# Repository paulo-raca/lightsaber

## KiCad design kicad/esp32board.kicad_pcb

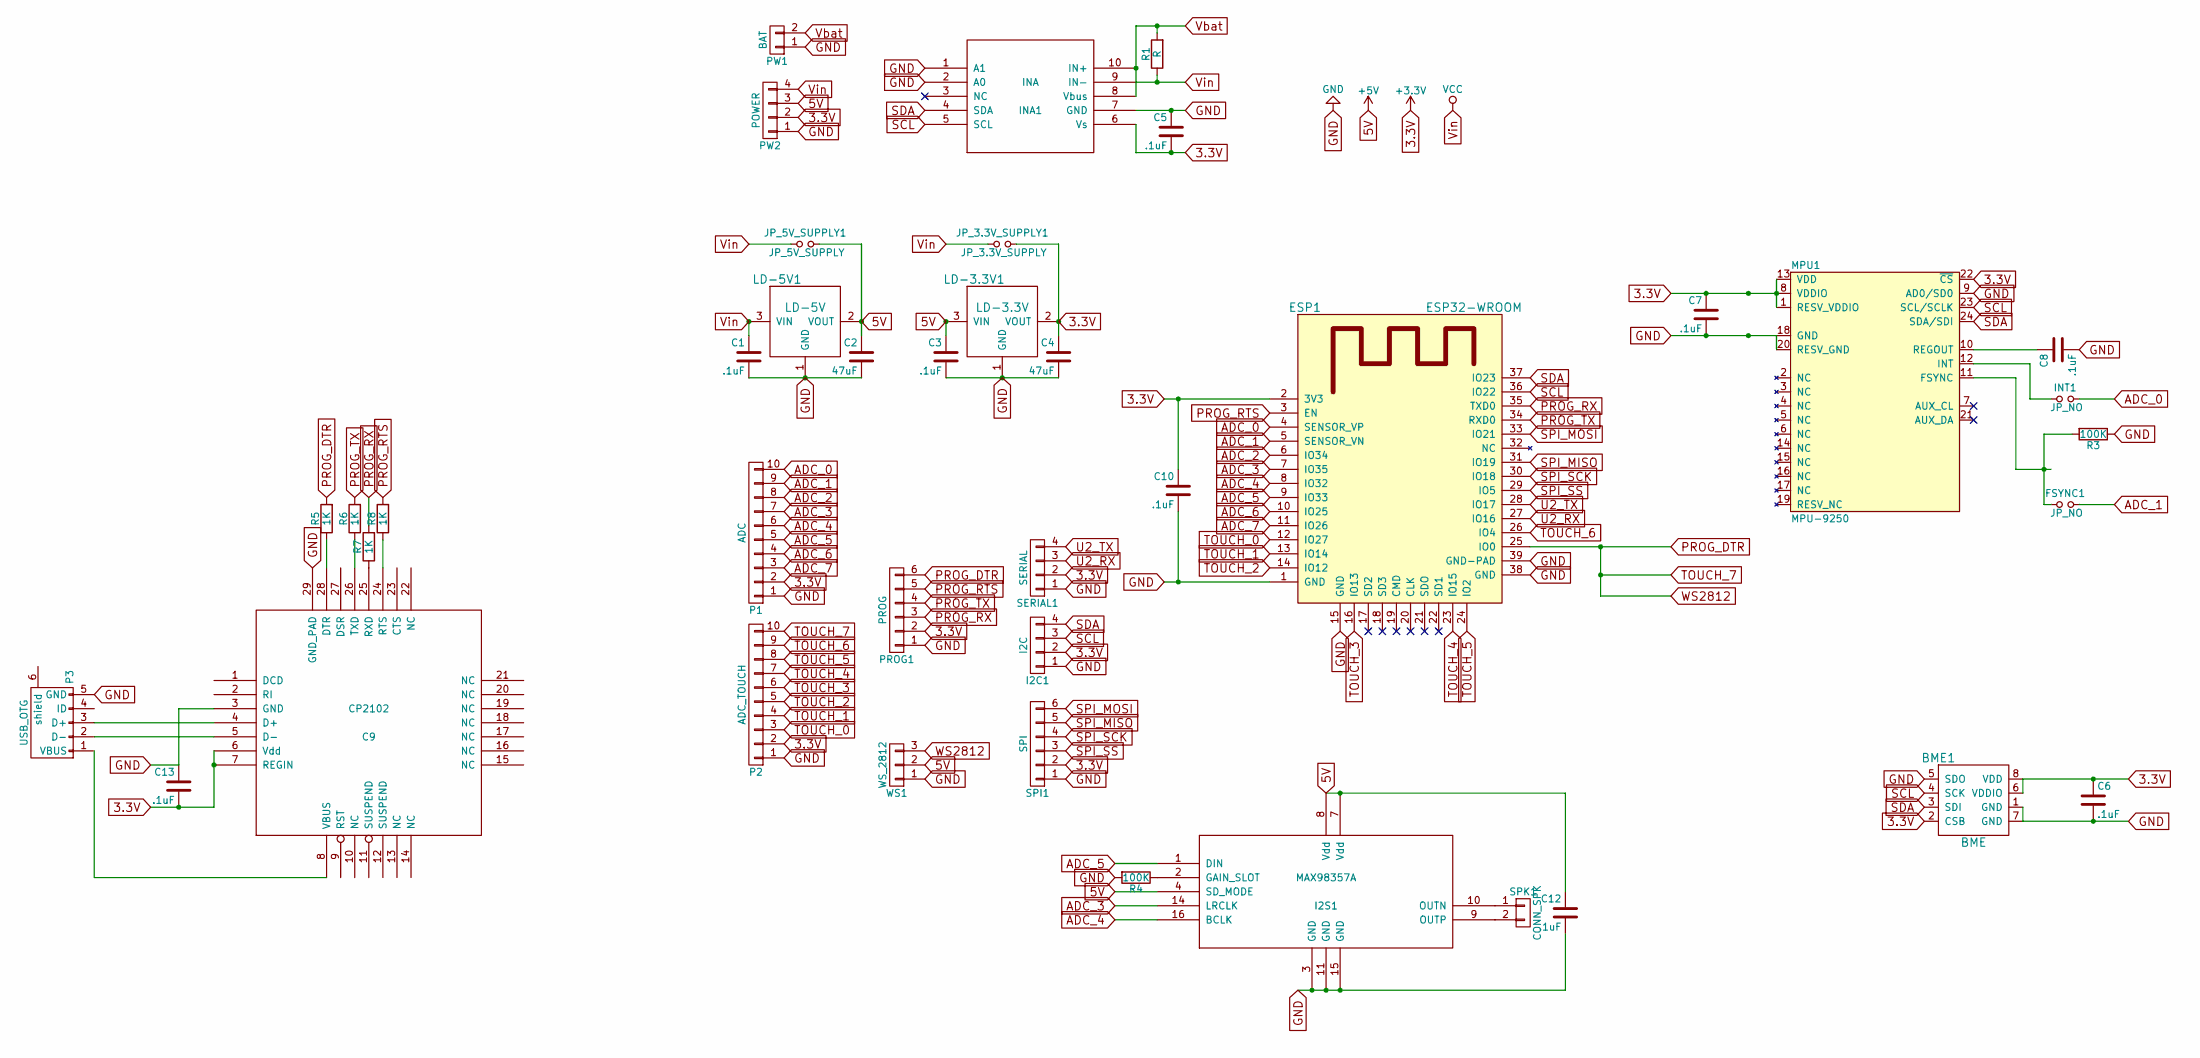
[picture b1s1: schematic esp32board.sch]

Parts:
BME1: BME; BME280
C1, C3, C5, C6, C7, C8, C10, C12, C13: .1uF; C_0603_HandSoldering
C2, C4: 47uF; C_0603_HandSoldering
C9: CP2102; QFN-28-1EP_5x5mm_Pitch0.5mm
ESP1: ESP32-WROOM
FSYNC1: JP_NO; SOLDER-JUMPER_1-WAY
I2C1: I2C; Pin_Header_Straight_1x04
I2S1: MAX98357A; QFN-16-1EP_3x3mm_Pitch0.5mm
INA1: INA; MSOP-10-1EP_3x3mm_Pitch0.5mm
INT1: JP_NO; SOLDER-JUMPER_1-WAY
JP_3.3V_SUPPLY1: JP_3.3V_SUPPLY; SOLDER-JUMPER_1-WAY
JP_5V_SUPPLY1: JP_5V_SUPPLY; SOLDER-JUMPER_1-WAY
LD-3.3V1: LD-3.3V; SOT-223
LD-5V1: LD-5V; SOT-223
MPU1: MPU-9250; QFN-24-MPU9250; DigiKey 1428-1019-1-ND
P1: ADC; Pin_Header_Straight_1x10
P2: ADC_TOUCH; Pin_Header_Straight_1x10
P3: USB_OTG; USB_Micro-B_Molex_47346-0001
PROG1: PROG; Pin_Header_Straight_1x06
PW1: BAT; Molex_KK-6410-02_02x2.54mm_Straight
PW2: POWER; Molex_KK-6410-04_04x2.54mm_Straight
R1: R; R_2816_HandSoldering
R3, R4: 100K; R_0603_HandSoldering
R5, R6, R7, R8: 1K; R_0603_HandSoldering
SERIAL1: SERIAL; Pin_Header_Straight_1x04
SPI1: SPI; Pin_Header_Straight_1x06
SPK1: CONN_SPK; Pin_Header_Straight_1x02
WS1: WS_2812; Pin_Header_Straight_1x03

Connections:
3.3V: BME1.2 (CSB), BME1.6 (VDDIO), BME1.8 (VDD), C4.1, C5.2, C6.1, C7.1, C9.6 (Vdd), C9.7 (REGIN), C10.1, C13.2, ESP1.2 (3V3), I2C1.2, INA1.6 (Vs), JP_3.3V_SUPPLY1.2, LD-3.3V1.2 (VOUT), MPU1.1 (RESV_VDDIO), MPU1.8 (VDDIO), MPU1.13 (VDD), MPU1.22 (~CS), P1.2, P2.2, PROG1.2, PW2.2, SERIAL1.2, SPI1.2
5V: C2.1, C3.1, C12.1, I2S1.4 (SD_MODE), I2S1.7 (Vdd), I2S1.8 (Vdd), JP_5V_SUPPLY1.2, LD-3.3V1.3 (VIN), LD-5V1.2 (VOUT), PW2.3, WS1.2
ADC_0: ESP1.4 (SENSOR_VP), INT1.2, P1.10
ADC_1: ESP1.5 (SENSOR_VN), FSYNC1.2, P1.9
ADC_2: ESP1.6 (IO34), P1.8
ADC_3: ESP1.7 (IO35), I2S1.14 (LRCLK), P1.7
ADC_4: ESP1.8 (IO32), I2S1.16 (BCLK), P1.6
ADC_5: ESP1.9 (IO33), I2S1.1 (DIN), P1.5
ADC_6: ESP1.10 (IO25), P1.4
ADC_7: ESP1.11 (IO26), P1.3
GND: BME1.1 (GND), BME1.5 (SDO), BME1.7 (GND), C1.2, C2.2, C3.2, C4.2, C5.1, C6.2, C7.2, C8.2, C9.3 (GND), C9.29 (GND_PAD), C10.2, C12.2, C13.1, ESP1.1 (GND), ESP1.15 (GND), ESP1.38 (GND), ESP1.39 (GND-PAD), I2C1.1, I2S1.3 (GND), I2S1.11 (GND), I2S1.15 (GND), I2S1.17 (GND_PAD), INA1.1 (A1), INA1.2 (A0), INA1.7 (GND), LD-3.3V1.1 (GND), LD-5V1.1 (GND), MPU1.9 (AD0/SD0), MPU1.18 (GND), MPU1.20 (RESV_GND), P1.1, P2.1, P3.5 (GND), PROG1.1, PW1.1, PW2.1, R3.1, R4.2, SERIAL1.1, SPI1.1, WS1.1
unnamed: C8.1, MPU1.10 (REGOUT)
unnamed: C9.4 (D+), P3.3 (D+)
unnamed: C9.5 (D-), P3.2 (D-)
unnamed: C9.8 (VBUS), P3.1 (VBUS)
unnamed: C9.24 (RTS), R8.1
unnamed: C9.25 (RXD), R7.1
unnamed: C9.26 (TXD), R6.1
unnamed: C9.28 (DTR), R5.1
unnamed: FSYNC1.1, MPU1.11 (FSYNC), R3.2
unnamed: I2S1.2 (GAIN_SLOT), R4.1
unnamed: I2S1.9 (OUTP), SPK1.2
unnamed: I2S1.10 (OUTN), SPK1.1
unnamed: INT1.1, MPU1.12 (INT)
PROG_DTR: ESP1.25 (IO0), P2.10, PROG1.6, R5.2, WS1.3
PROG_RTS: ESP1.3 (EN), PROG1.5, R8.2
PROG_RX: ESP1.35 (TXD0), PROG1.3, R7.2
PROG_TX: ESP1.34 (RXD0), PROG1.4, R6.2
SCL: BME1.4 (SCK), ESP1.36 (IO22), I2C1.3, INA1.5 (SCL), MPU1.23 (SCL/SCLK)
SDA: BME1.3 (SDI), ESP1.37 (IO23), I2C1.4, INA1.4 (SDA), MPU1.24 (SDA/SDI)
SPI_MISO: ESP1.31 (IO19), SPI1.5
SPI_MOSI: ESP1.33 (IO21), SPI1.6
SPI_SCK: ESP1.30 (IO18), SPI1.4
SPI_SS: ESP1.29 (IO5), SPI1.3
TOUCH_0: ESP1.12 (IO27), P2.3
TOUCH_1: ESP1.13 (IO14), P2.4
TOUCH_2: ESP1.14 (IO12), P2.5
TOUCH_3: ESP1.16 (IO13), P2.6
TOUCH_4: ESP1.23 (IO15), P2.7
TOUCH_5: ESP1.24 (IO2), P2.8
TOUCH_6: ESP1.26 (IO4), P2.9
U2_RX: ESP1.27 (IO16), SERIAL1.3
U2_TX: ESP1.28 (IO17), SERIAL1.4
Vbat: INA1.8 (Vbus), INA1.10 (IN+), PW1.2, R1.2
Vin: C1.1, INA1.9 (IN-), JP_3.3V_SUPPLY1.1, JP_5V_SUPPLY1.1, LD-5V1.3 (VIN), PW2.4, R1.1

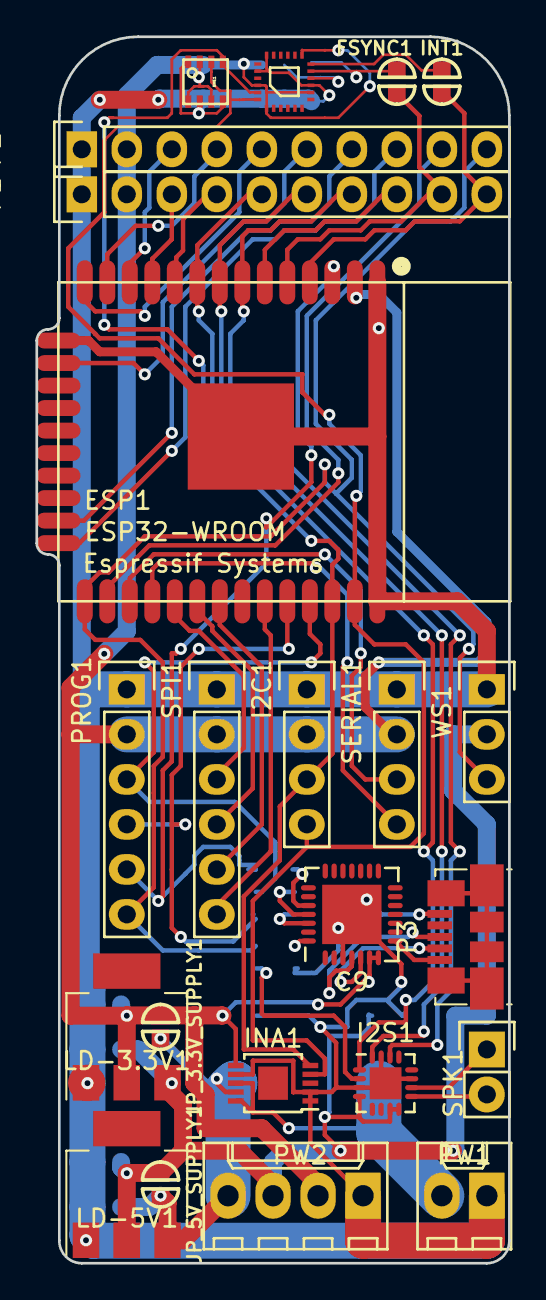
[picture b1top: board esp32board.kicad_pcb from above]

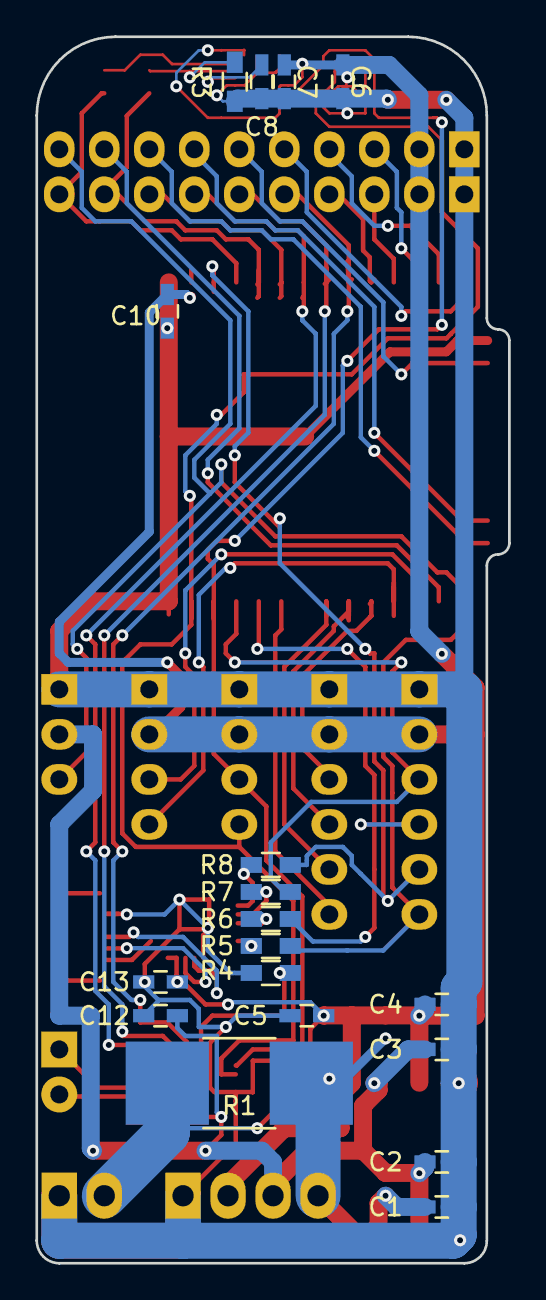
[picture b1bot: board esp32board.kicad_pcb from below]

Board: 2 copper layers, 26.7 x 69.2 mm, 41 parts (18 on the bottom side), 45 nets.

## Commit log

2017-08-08 PCB v1
2017-08-09 Added I2S amplifier (Incomplete)
2017-08-16 Finished board layout
2017-08-16 Added openscad files
2017-08-17 1.25" tube actually has 1.40" ?!
    On the other hand, the extra space means I can use a 1" tube (Which actually has 1,1"!)
2017-08-24 Added battery holder
